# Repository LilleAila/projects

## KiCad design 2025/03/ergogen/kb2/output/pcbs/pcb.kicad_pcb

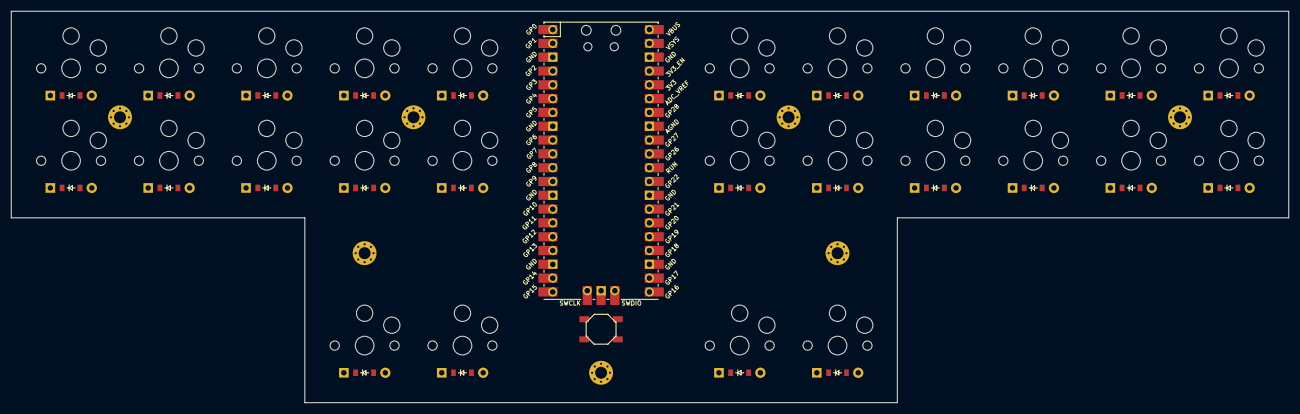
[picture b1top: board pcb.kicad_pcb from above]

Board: 2 copper layers, 235.0 x 72.0 mm, 61 parts (0 on the bottom side), 30 nets, no tracks yet.

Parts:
B1: SW_TACT_ALPS_SKQGABE010
D1, D2, D3, D4, D5, D6, D7, D8, D9, D10, D11, D12, D13, D14, D15, D16, D17, D18, D19, D20, D21, D22, D23, D24, D25, D26: ComboDiode
S1, S2, S3, S4, S5, S6, S7, S8, S9, S10, S11, S12, S13, S14, S15, S16, S17, S18, S19, S20, S21, S22, S23, S24, S25, S26: PG1350
_1: RPi_Pico_SMD_TH
_2, _3, _4, _5, _6, _7, _8: MountingHole_2.2mm_M2_Pad_Via

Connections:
GND: B1.1, _1.3, _1.8, _1.13, _1.18, _1.23, _1.28, _1.38
GP5: D2.1, D4.1, D6.1, D8.1, D10.1, _1.7
GP9: D1.1, D3.1, D5.1, D7.1, D9.1, _1.12
GP10: S9.1, S10.1, S24.1, _1.14
GP11: S7.1, S8.1, S23.1, _1.15
GP12: S5.1, S6.1, _1.16
GP13: S3.1, S4.1, _1.17
GP14: S1.1, S2.1, _1.19
GP15: D23.1, D24.1, D25.1, D26.1, _1.20
GP16: S21.1, S22.1, _1.21
GP17: S19.1, S20.1, _1.22
GP18: S17.1, S18.1, _1.24
GP19: S15.1, S16.1, _1.25
GP20: S13.1, S14.1, S26.1, _1.26
GP21: S11.1, S12.1, S25.1, _1.27
GP22: D11.1, D13.1, D15.1, D17.1, D19.1, D21.1, _1.29
GP28: D12.1, D14.1, D16.1, D18.1, D20.1, D22.1, _1.34
RUN: B1.2, _1.30
index_bottom: D7.2, D13.2, S7.2, S13.2
index_top: D8.2, D14.2, S8.2, S14.2
inner_bottom: D9.2, D11.2, S9.2, S11.2
inner_top: D10.2, D12.2, D24.2, D25.2, S10.2, S12.2, S24.2, S25.2
middle_bottom: D5.2, D15.2, S5.2, S15.2
middle_top: D6.2, D16.2, S6.2, S16.2
outer_bottom: D21.2, S21.2
outer_top: D22.2, D23.2, D26.2, S22.2, S23.2, S26.2
pinky_bottom: D1.2, D19.2, S1.2, S19.2
pinky_top: D2.2, D20.2, S2.2, S20.2
ring_bottom: D3.2, D17.2, S3.2, S17.2
ring_top: D4.2, D18.2, S4.2, S18.2
